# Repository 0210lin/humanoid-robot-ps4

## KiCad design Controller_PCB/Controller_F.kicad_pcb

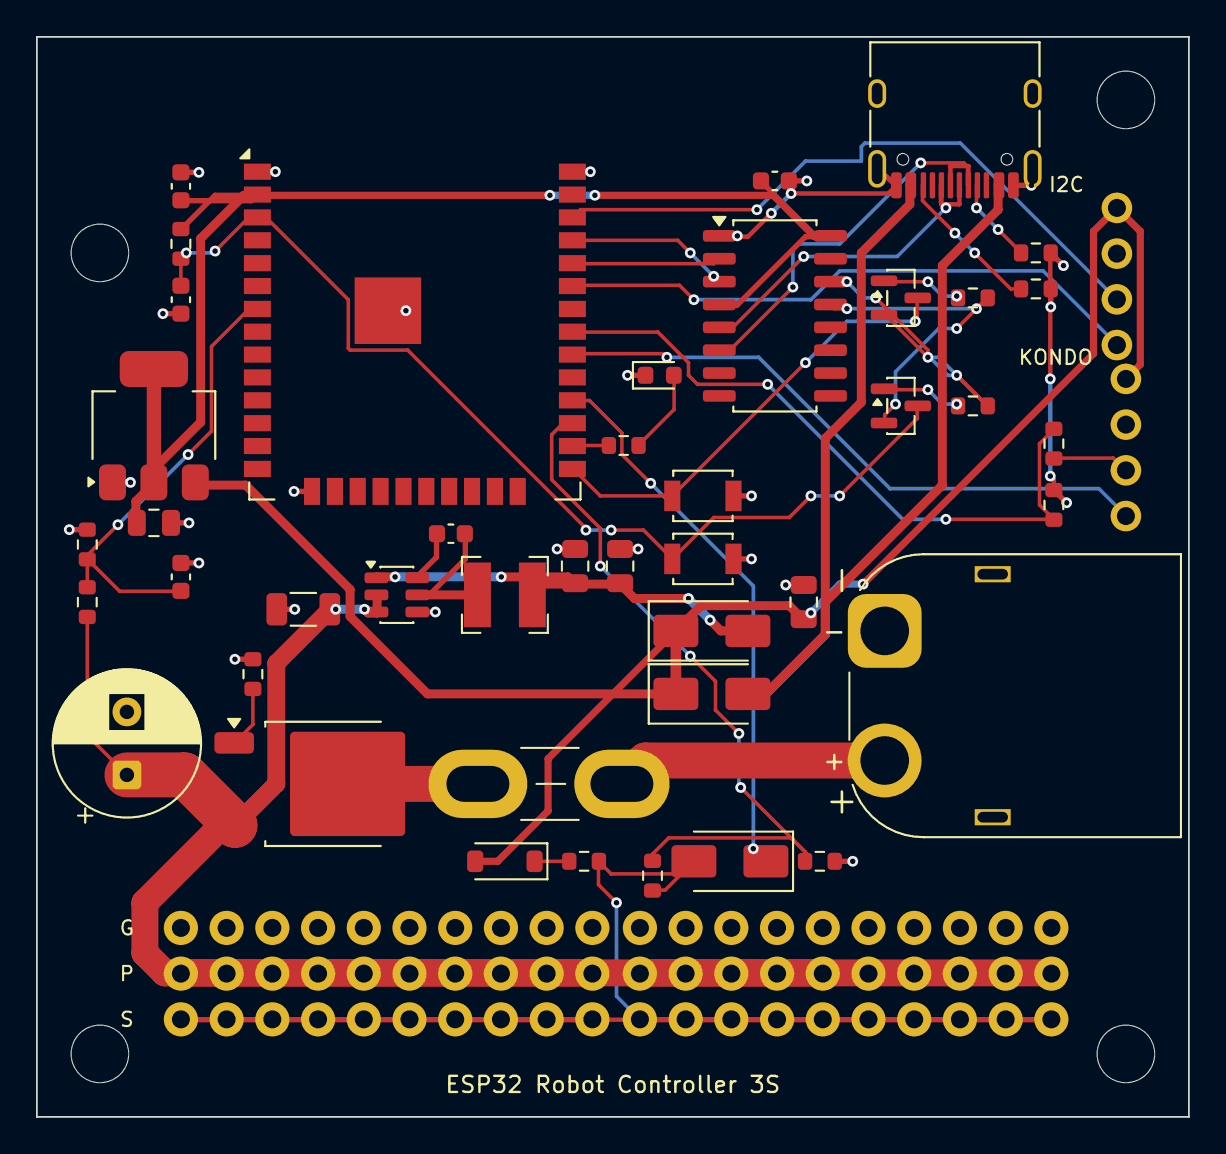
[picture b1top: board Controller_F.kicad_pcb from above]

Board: 2 copper layers, 64.0 x 60.0 mm, 50 parts (0 on the bottom side), 35 nets.

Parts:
C1: 10uF 25V; C_1206_3216Metric
C2, C4, C6: 22uF; C_0805_2012Metric
C3, C7, C8, C10: 100nF; C_0603_1608Metric
C5: 10uF; C_0805_2012Metric
C9: 1uF; C_0603_1608Metric
C11: 470uF 25V; CP_Radial_D8.0mm_P3.50mm
D1: 1N4148W; D_SOD-123
D2, D3, D4: SS14; D_SMA
D5: LED; LED_0603_1608Metric
F1: Mini blade fuse; Fuse_Blade_Mini_directSolder
H1, H2, H3, H4: MountingHole_3.2mm_M3
J1: XT60PW-M; AMASS_XT60PW-M_1x02_P7.20mm_Horizontal
J3: USB-C; USB_C_Receptacle_HRO_TYPE-C-31-M-12
J4: I2C
J5: SERVO x20
J6: KONDO
L1: 4.7uH; L_Bourns-SRN4018
Q1: CJU40P03; TO-252-2_DPAK
Q2, Q3: MMBT3904; SOT-23
R1: 3.3k; R_0603_1608Metric
R2, R5, R16: 22k; R_0603_1608Metric
R3, R17: 47k; R_0603_1608Metric
R4, R6: 100k; R_0603_1608Metric
R7, R11, R12: 10k; R_0603_1608Metric
R9, R10: 5.1k; R_0603_1608Metric
R13: 1k; R_0603_1608Metric
SW1: RESET; SW_SPST_B3U-1000P
SW2: BOOT; SW_SPST_B3U-1000P
U1: AP63205WU-7; TSOT-23-6
U2: ESP32-WROOM-32E
U3: AMS1117-3.3; SOT-223-3_TabPin2
U4: CH340C; SOP-16_4.4x10.4mm_P1.27mm

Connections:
3V3: C6.1, C7.1, C10.1, R7.2, U2.2, U3.2, U4.4, U4.16
B2: Q2.1, R11.2
B3: Q3.1, R12.2
BAT_FUSED: F1.1, Q1.2
BAT_RAW: F1.2, J1.2
BST: C3.2, U1.6
CC1: J3.A5, R9.1
CC2: J3.B5, R10.1
DM: J3.A7, J3.B7, U4.6
DP: J3.A6, J3.B6, U4.5
DTR: Q3.2, R11.1, U4.13
EN: C9.2, Q3.3, R7.1, SW1.1, U2.3
GATE: Q1.1, R6.1
GND: C1.1, C2.2, C4.2, C5.2, C6.2, C7.2, C8.2, C9.1, C10.2, C11.2, D5.1, J1.1, J3.A1, J3.A12, J3.B1, J3.B12, J3.SH, J4.2, J5.G1, J5.G2, J5.G3, J5.G4, J5.G5, J5.G6, J5.G7, J5.G8, J5.G9, J5.G10, J5.G11, J5.G12, J5.G13, J5.G14, J5.G15, J5.G16, J5.G17, J5.G18, J5.G19, J5.G20, J6.2, R3.1, R5.2, R6.2, R9.2, R10.2, R17.2, SW1.2, SW2.2, U1.4, U2.1, U2.15, U2.38, U2.39, U3.1, U4.1
IO0: Q2.3, SW2.1, U2.25
KRX: J6.3, R16.1
KRXG: R16.2, R17.1, U2.31
KTX: J6.4, U2.30
LED: R13.1, U2.26
LEDA: D5.2, R13.2
PU: D1.1, R1.2
RTS: Q2.2, R12.1, U4.14
RX: R2.1, R3.2, U2.27
SCL: J4.3, U2.36
SDA: J4.4, U2.33
SIG: D2.2, J5.S1, J5.S2, J5.S3, J5.S4, J5.S5, J5.S6, J5.S7, J5.S8, J5.S9, J5.S10, J5.S11, J5.S12, J5.S13, J5.S14, J5.S15, J5.S16, J5.S17, J5.S18, J5.S19, J5.S20, R1.1, R2.2
SW: C3.1, L1.1, U1.5
TX: D2.1, U2.28
U0RX: U2.34, U4.2
U0TX: U2.35, U4.3
V5: C2.1, C4.1, D3.2, L1.2, U1.1
V5S: C5.1, D1.2, D3.1, D4.1, J4.1, J6.1, U3.3
VBAT: C1.2, C11.1, J5.P1, J5.P2, J5.P3, J5.P4, J5.P5, J5.P6, J5.P7, J5.P8, J5.P9, J5.P10, J5.P11, J5.P12, J5.P13, J5.P14, J5.P15, J5.P16, J5.P17, J5.P18, J5.P19, J5.P20, Q1.3, R4.1, U1.2, U1.3
VBUS: D4.2, J3.A4, J3.A9, J3.B4, J3.B9
VSENSE: C8.1, R4.2, R5.1, U2.7

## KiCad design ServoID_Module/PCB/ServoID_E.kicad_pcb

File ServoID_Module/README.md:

# ServoID 模組:用手機編伺服馬達 ID

換馬達時,把新馬達插在模組上,用手機(iPhone / Android 都行,不用裝 App)連模組的 WiFi,開網頁就能:
**掃描 → 改 ID → 讀回確認 → 測試轉動**,然後直接裝回機器人。

> **狀態:韌體已寫好、能編譯、封包格式已用 PDF 和原廠工具的範例驗證;電路和韌體都還沒有在真的硬體上測試過。**
> 第一次請照下面「第一次通電」的順序做,先用一顆**不要的馬達**。

## 選哪塊 ESP32

| 板子 | 用途 | 編譯目標 | 腳位(TX / RX / 電池偵測) |
|---|---|---|---|
| **M5Stack ATOM Lite** | 麵包板原型(目前在用) | `esp32:esp32:m5stack-atom` | G22 / G19 / G33 |
| **ESP32-C3 SuperMini**(約 22.5×18 mm,2.54 mm 排針孔,USB-C,便宜) | **最後做成一塊板子,最好焊** | `esp32:esp32:esp32c3:CDCOnBoot=cdc` | GPIO7 / GPIO6 / GPIO3,LED = GPIO8 |
| Seeed XIAO ESP32-C3 | 也可以 | `esp32:esp32:XIAO_ESP32C3:CDCOnBoot=cdc` | D5 / D4 / D1 |

- 做成一塊板子時,建議用 **ESP32-C3 SuperMini**:它的腳是一般 2.54 mm 間距的排針孔,可以直接焊在洞洞板或自己的電路板上,不用處理貼片。
- **注意**:SuperMini 有些批次的 WiFi 天線效果比較差,訊號距離會短,但貼著手機用沒問題。要用之前建議先用一片測試 WiFi 連線是否穩定。
- 裸的 ESP32 模組(貼片)比較難手焊,不建議。
- 三種板子是同一份韌體,編譯時依晶片自動選腳位。

## 零件(麵包板版,不用焊接)

| 零件 | 說明 |
|---|---|
| Seeed XIAO ESP32-C3 | 主控,內建 WiFi、USB-C 燒錄 |
| 降壓模組(輸入 6~16 V、輸出 5 V、≥ 500 mA) | MP1584 類。**先單獨通電,用三用電表調到 5.0 V,再接 XIAO** |
| 1N4148 ×1 | 匯流排上拉的串聯二極體(模仿原廠轉接板,空閒約 4.1~4.2 V) |
| BAT54 或 1N5819 ×1 | 送出資料用(蕭特基) |
| 1N5819 ×1 | 降壓輸出到 XIAO 5V 腳之間,防止 USB 和電池同時接時倒灌 |
| 電阻 3.3 kΩ、22 kΩ、47 kΩ、100 kΩ、22 kΩ 各 1 | 上拉、Sig 分壓、電池分壓 |
| XT60 帶線母頭 | 接電池 |
| 保險絲(3~5 A,自恢復也行) | 串在電池正極 |
| 3 針接頭(和馬達同規格) | Gnd / 電源 / Sig,插馬達 |
| 20~22 AWG 矽膠線、迷你麵包板 | |

## 接線

> 電路圖:[`schematic.svg`](schematic.svg)(向量圖,可放大)/ [`schematic.png`](schematic.png)。下面的文字圖是簡化版,**以電路圖為準**。

```
電池 XT60 +  ──[保險絲]──┬────────────────────→ 馬達接頭「電源」針(紅)
                           └→ 降壓模組 IN+
電池 XT60 −  ───────────────┬──────────────────→ 馬達接頭「Gnd」針(黑)
                            └→ 降壓 GND ── XIAO GND

降壓 OUT+(5V) ─[1N5819]─→ XIAO 5V 腳
降壓 OUT+(5V) ─[1N4148]─[3.3kΩ]─┬─→ Sig 節點 = 馬達接頭「Sig」針(白)
                                   │
                  BAT54 陽極 ───────┤   BAT54 陰極 → XIAO D5(GPIO7,TX)
                                   │
                          22kΩ ────┘→ XIAO D4(GPIO6,RX) ──47kΩ── GND

電池分壓:電池 + ─100kΩ─ XIAO D1(GPIO3) ─22kΩ─ GND
```

腳位(韌體編譯時依晶片自動選):

| | XIAO ESP32-C3 | **M5Stack ATOM Lite** |
|---|---|---|
| 匯流排 TX(接 BAT54 陰極) | D5(GPIO7) | **G22** |
| 匯流排 RX(接 Sig 分壓) | D4(GPIO6) | **G19** |
| 電池電壓偵測 | D1(GPIO3) | **G33**(ADC1,WiFi 開著也能量) |
| 供電 | 5V 腳 | **5V 腳**(從降壓模組的 5 V 接進來) |
| LED | 板上 D10 | G27 全彩 LED(匯流排有動作時亮青色) |

ATOM Lite 的 G22、G19、G33 在底部排針上,**請對照板子上的絲印確認**(我是依 M5Stack 的腳位圖,沒有拿到實物)。要改腳位,改 `ServoID_Module.ino` 最上面。

**原理(單線 UART)**:匯流排平常被上拉到高電位;送資料時 TX 拉低,二極體導通把匯流排拉低,TX 為高時二極體截止,由上拉維持高電位;接收則把匯流排經分壓降到 ESP32 能承受的電壓(Sig 4.1 V → RX 約 2.8 V)。單線會聽到自己送出的資料(回音),韌體會先讀掉,並檢查回音是否正確(不正確 = RX 接線有問題)。

## 燒錄

**M5Stack ATOM Lite**(先用它做原型):
```
Tools_Arduino\arduino-cli.exe board list                                  找出 ATOM Lite 的 COM 埠
Tools_Arduino\arduino-cli.exe compile --fqbn esp32:esp32:m5stack-atom ServoID_Module
Tools_Arduino\arduino-cli.exe upload  --fqbn esp32:esp32:m5stack-atom -p COM你的埠 ServoID_Module
```

**XIAO ESP32-C3**:
```
Tools_Arduino\arduino-cli.exe compile --fqbn esp32:esp32:XIAO_ESP32C3:CDCOnBoot=cdc ServoID_Module
Tools_Arduino\arduino-cli.exe upload  --fqbn esp32:esp32:XIAO_ESP32C3:CDCOnBoot=cdc -p COM你的埠 ServoID_Module
```

**只想先測 WiFi 和網頁**:不用接任何外部電路,燒錄後 ATOM 只靠 USB 供電就會開 WiFi,手機連上去能開網頁(電池會顯示「沒接電池」,掃描會找不到馬達,這是正常的)。

開機後序列監控(115200)會印 `[自我檢查] 封包格式 全部 PASS` 和 WiFi 熱點名稱。

## 手機操作

1. 手機 WiFi 連 **ServoID-XXXX**,密碼 **servoid1234**(韌體裡 `AP_PASS` 可改)。iPhone 會說「沒有網路」,不用理它。
2. 瀏覽器開 **http://192.168.4.1**。
3. **步驟 1(最重要)**:先只接電池、**不要插馬達**。網頁顯示電池電壓和 2S / 3S。選你要編的馬達是 7.4 V 還是 12 V,**電池和選的電壓不符時網頁會用紅字警告**,這時絕對不要插馬達。
4. 確認相符後才插馬達。
5. **掃描**:找出馬達現在是幾號。只找到 1 顆才能改 ID。
6. **改 ID**:選新號碼 → 按按鈕。韌體會寫入、等 1.5 秒、讀回確認,並檢查舊 ID 已經消失。
7. **測試轉動**:馬達要空載(不掛任何東西)。會往中點方向小幅轉動再回來,並讀回位置確認。
   **微調 −100 / +100**:每按一次動 100 單位(約 16°),以第一次按時的位置當原位,最多離原位 ±100;「回原位」可以回去。電池電壓和選的馬達不符時這些按鈕會鎖住。
8. 電池電壓不準時校正:用三用電表量電池,瀏覽器開 `http://192.168.4.1/api/cal?v=實測電壓`(例如 `?v=7.52`)。

## 2026-10-14 新功能

- **電腦版 `ServoID_Tool.exe` 可以用 USB 線**:模組用 USB 接電腦,開程式後「連線方式」選「USB 線:COMx(ESP32)」(偵測到會自動選),不用連 WiFi、電腦也不會斷網。也可以選 WiFi。模組重開機後會自動重新連上。
- **分頁(電腦版和手機網頁功能一樣)**:
  - **編 ID 與測試**:原本的四個步驟,加上「來回掃」。
  - **網路設定**(電腦版是第三個分頁;手機在第一頁最下面):見下面「網路」。
  - **多顆馬達**:掃描列出全部(點號碼,那顆會左右動一下,方便認出是哪一顆)、**全部改成同一個 ID**、**全部一起來回轉**(不管 ID,用眼睛看哪顆不正常)、全部回中 1500、全部放鬆。「全部」類的指令是對 1~127 每個號碼各送一次,不用廣播。
- **網路**:
  - **每塊板子有自己的熱點**:名稱和密碼出貨時用 USB 寫進板子(`ps4 test\ServoID_出貨\出貨設定.ps1`,買家清單在同一個資料夾,不要上傳)。沒寫過的板子(自己這塊)是 HurtMakerID。買家可以在網頁改熱點**密碼**(名稱不能改);**按住 BOOT 3 秒,密碼回到出廠密碼**。
  - **模組要去找的網路(只能一個)**:第一次開網頁會問要不要設定。設定後模組會連上那個網路(例如手機熱點),熱點照樣開著;在那個網路上開 **http://servoid.local**(iPhone 熱點通常也可以開 http://172.20.10.2)。只能連 2.4 GHz,iPhone 熱點要打開「最大化相容性」。網頁可以掃描附近的網路用點的選。
  - 這些設定存在板子裡,重新燒韌體不會不見。
- **iPhone 不會自己斷開模組的 WiFi**:模組會回應手機的「有沒有網路」檢查。
- **USB 和電池可以同時接**(板子上有二極體隔開)。
- **燒錄 ESP32-C3 SuperMini**:自動進下載模式常常失敗,請**按住 BOOT → 按一下 RST → 放開 BOOT** 再燒;燒完**按一下 RST**(不要按 BOOT)才會開始執行。接著電池時,只拔插 USB 不會讓模組重開機。

## 第一次通電(請照順序)

1. **只接 USB**(沒電池、沒馬達):手機能連上 WiFi、網頁打得開。序列監控看到自檢 PASS。
2. 降壓模組**單獨**接電池,用三用電表量輸出,調到 **5.0 V**。調好才接到 XIAO。
3. 接電池(不接馬達):網頁電壓應該接近你三用電表量到的值;不準就用 `/api/cal` 校正。
4. 用三用電表量 **Sig 對 Gnd** 的空閒電壓,應該約 **4.0~4.2 V**(你原廠轉接板量到 4.2 V)。差太多先不要插馬達。
5. 插一顆**不要的馬達**:掃描 → 應該找到 1 顆。
6. 讀狀態、測試轉動、改 ID、再掃描確認。
7. 都正常再拿來編要上機器人的馬達。

## 安全設計

- 韌體**永遠不會送廣播(ID 0)的寫入指令**(`servobus.h` 裡 ID 0 會被拒絕,開機自檢也會檢查)。
- 改 ID 前先掃描 1~127:找到的馬達不是剛好 1 顆就拒絕。(例外:「多顆馬達」頁的「全部改成同一個 ID」,會先掃描給你確認,預設按鈕是取消;**不要接在機器人上用**。)
- 測試轉動只有在「電池電壓和你選的馬達電壓相符、電量不低」時才允許;位置夾在 800~2200(PDF 的有效範圍);角度只有 100~250 單位(約 16~41°)。
- **模組不能切斷馬達電源**:電池是直通馬達的。插錯電池(例如 12 V 接到 7.4 V 的馬達)馬達就會直接承受,韌體擋不住。所以**一定要先接電池看電壓,確認後才插馬達**。

## 已知限制 / 沒驗證的

- 電路(上拉 3.3 kΩ、分壓 22 kΩ / 47 kΩ、單二極體送出)在 500000 baud 下的波形夠不夠乾淨,**要實測**(最好用示波器)。不夠的話改用電晶體做開集極輸出,TX 腳用 `uart_set_line_inverse` 反相。
- 「讀 ID 暫存器」的回應格式是依 PDF 推論的(寫 ID 的封包是從原廠工具程式取得);讀回失敗時先用原廠工具確認馬達狀態。
- 電壓、電流、溫度暫存器只顯示原始值(0~1023),換算係數我不知道。
- 沒有做「輸出功率上限」:暫存器位址 4 在 PDF 裡是可寫的,但原廠工具沒用它,我沒驗證,所以不敢放進韌體。
- 預設 WiFi 密碼寫死在韌體裡,只適合在自己手邊使用。

## 檔案

- `ServoID_Module.ino`:主程式(WiFi、網頁 API、掃描、改 ID、測試)
- `servobus.h`:封包產生(純 C++,ID 0 一律拒絕)
- `webpage.h`:手機網頁

## 協定來源

- ServoBus protocol V0.5 PDF
- 原廠 `CAS_Servo_Management` 工具(用靜態分析讀出的封包):
  - Ping:`[ID|0x80] 81 [CS]`
  - 改 ID:`[目前ID|0x80] 92 20 00 [新ID] [CS]`(位址 32,值的低位元組 = ID)
  - 設位置:`[ID|0x80] 83 05 位置高 位置低 時間高 時間低 [CS]`,放鬆 = 位置 0
  - 讀暫存器:`[ID|0x80] 91 長度 位址 [CS]`(位置 5、電壓 7、電流 8、溫度 9、ID 32)
  - 檢查碼 = 前面所有位元組相加取低 8 位元,500000 baud 8N1,結尾沒有 0xFF

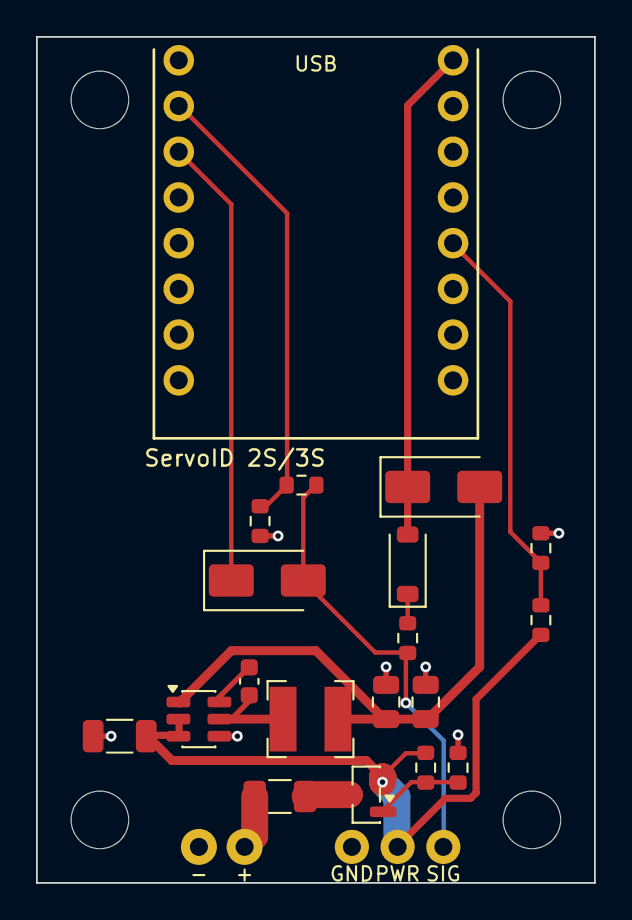
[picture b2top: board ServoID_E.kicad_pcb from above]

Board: 2 copper layers, 31.0 x 47.0 mm, 25 parts (0 on the bottom side), 14 nets.

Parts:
C1: 10uF 25V; C_1206_3216Metric
C2, C4: 22uF; C_0805_2012Metric
C3: 100nF; C_0603_1608Metric
D1: 1N4148W; D_SOD-123
D2, D3: SS14; D_SMA
F1: 5A; Fuse_1206_3216Metric
H1, H2, H3, H4: MountingHole_3.2mm_M3
J1: BATTERY
J2: MOTOR
L1: 4.7uH; L_Bourns-SRN4018
Q1: AO3401A; SOT-23
R1: 3.3k; R_0603_1608Metric
R2, R5: 22k; R_0603_1608Metric
R3: 47k; R_0603_1608Metric
R4, R6, R7: 100k; R_0603_1608Metric
U1: AP63205WU-7; TSOT-23-6
U2: ESP32-C3 SuperMini

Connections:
BAT_FUSED: F1.2, Q1.3
BAT_RAW: F1.1, J1.2
BST: C3.2, U1.6
GATE: Q1.1, R6.1, R7.1
GND: C1.1, C2.2, C4.2, J1.1, J2.1, R3.1, R5.2, R7.2, U1.4, U2.R2
PU: D1.1, R1.2
RX: R2.1, R3.2, U2.L2
SIG: D2.2, J2.3, R1.1, R2.2
SW: C3.1, L1.1, U1.5
TX: D2.1, U2.L3
V5: C2.1, C4.1, D3.2, L1.2, U1.1
V5S: D1.2, D3.1, U2.R1
VBAT: C1.2, J2.2, Q1.2, R4.1, R6.2, U1.2, U1.3
VSENSE: R4.2, R5.1, U2.R5

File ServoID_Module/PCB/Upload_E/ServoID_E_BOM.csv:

Comment,Designator,Footprint,Quantity,LCSC Part #
10uF 25V,C1,C_1206_3216Metric,1,C13585
22uF,"C2,C4",C_0805_2012Metric,2,C45783
100nF,C3,C_0603_1608Metric,1,C14663
1N4148W,D1,D_SOD-123,1,C81598
SS14,"D2,D3",D_SMA,2,C2480
5A,F1,Fuse_1206_3216Metric,1,C48332
4.7uH,L1,L_Bourns-SRN4018,1,C48427
AO3401A,Q1,SOT-23,1,C15127
3.3k,R1,R_0603_1608Metric,1,C22978
22k,"R2,R5",R_0603_1608Metric,2,C31850
47k,R3,R_0603_1608Metric,1,C25819
100k,"R4,R6,R7",R_0603_1608Metric,3,C25803
AP63205WU-7,U1,TSOT-23-6,1,C2071056
Pin header 1x2P 2.54mm right angle,J1,PinHeader_1x02_P2.54mm_Horizontal,1,C54907645
Pin header 1x3P 2.54mm right angle,J2,PinHeader_1x03_P2.54mm_Horizontal,1,C54907646
Female header 1x8P 2.54mm vertical,"J3,J4",PinSocket_1x08_P2.54mm_Vertical,2,C27438

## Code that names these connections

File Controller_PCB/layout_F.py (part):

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    ("D4", "Diode_SMD", "D_SMA", 37.5, 36.5, 0, "SS14", {"1": "V5S", "2": "VBUS"}),
    ("C5", "Capacitor_SMD", "C_0805_2012Metric", 42.6, 31.4, 90, "10uF", {"1": "V5S", "2": "GND"}),
    # --- 3.3V ---
    ("U3", "Package_TO_SOT_SMD", "SOT-223-3_TabPin2", 6.5, 21.6, 90, "AMS1117-3.3", {"1": "GND", "2": "3V3", "3": "V5S"}),
    ("C6", "Capacitor_SMD", "C_0805_2012Metric", 6.5, 27.0, 0, "22uF", {"1": "3V3", "2": "GND"}),
    ("C10", "Capacitor_SMD", "C_0603_1608Metric", 8.0, 8.3, 90, "100nF", {"1": "3V3", "2": "GND"}),
    # --- EN / BOOT / 重置 ---
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    ("GND", 0.25, "R9.2", "R10.2"), ("GND", 0.25, "R10.2", "R17.2"), ("GND", 0.25, "J3.A12", "U4.1"),
    ("KRX", 0.2, "J6.3", "R16.1"), ("KRXG", 0.2, "R16.2", "R17.1"), ("KRXG", 0.2, "R17.1", "U2.31"), ("KTX", 0.2, "J6.4", "U2.30"),
]
J4_PINS = {"1": "V5S", "2": "GND", "3": "SCL", "4": "SDA"}
J6_PINS = {"1": "V5S", "2": "GND", "3": "KRX", "4": "KTX"}
LABELS = [("I2C", 57.2, 8.2), ("KONDO", 56.6, 17.8)]

# USB-C 的 D+ / D- 兩組焊盤交錯,連接線手動畫(焊盤端點外側繞過去)
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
